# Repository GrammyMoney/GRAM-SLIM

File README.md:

# GRAM Slim

# Introduction 
**GRAM Slim** is a modular low-profile 21-button controller designed for Smash and FGC games. It has the standard pinout for firmwares like HayBox and Pico-Rectangle, and is also compatible with more fleshed-out FGC firmwares like GP2040-CE. With industrial design from GRAM, and PCB designed in collaboration with Quark.Works, this guide goes over a DIY-friendly approach to building the original GRAM Slim, and future guides/repos may hold remixes and modifications.

**If you would like to support the developer of this project, consider purchasing parts like buttons, PCBs, USB-C to GCC cables, and official GRAM builds at [GRAMCTRL.COM](https://www.gramctrl.com) rather than a fab house.**

Included Files
-
Included in this repo is all the files needed to get started with a simple GRAM Slim build:
- **GRAM Slim Frame .stl files**
- **Fab files for top and bottom panels**
- **Template DXF** for customizing top and bottom panels
- **GRAM 24mm keycap button .stl files**

Additional Information
-
If you want more info around GRAM builds, both open source and official builds, please join the [GRAM Digital Controllers Discord](https://discord.gg/6TuHw2r2X4) to ask questions and work with the community! I would love to see people creating new interesting designs, and building upon the initial framework.

Thanks & Acknowledgements
-
There are several people who made this project possible, either directly or indirectly.
- [Quark](https://twitter.com/quark_works), who did the PCB design on this and many other GRAM projects.
- [Bjart](https://twitter.com/bjartskular2), who developed the OFOF1 chassis, which was the initial development for a lot of the ideas explored in this build, including using PCB fabs for the panels, and the general idea of stacking two panels on a frame for the enclosure.
- My life and business partner [BRUISES](https://twitter.com/bruisesxo), who has turned GRAM into what it is today, and had incredible patience with me as I toiled away at my computer late into the night designing this thing.

# Ordering & Customization Guide
While most of these files are universal and can be used at any fab house, **JLCPCB** has become the de-facto standard for DIY box manufacturing. This is due to their hyper-affordable pricing and low minimum order quantity.

Bill of Materials
-
Per GRAM Slim, you will need (some files can be made using this repository, but I will link to places to purchase them if you would like to avoid MOQs)
- 1 x [GRAM Slim PCB](https://gramctrl.com/products/gram-slim-pcb)
- 1 x set of [Top/Bottom panels](https://gramctrl.com/products/gram-slim-aluminum-panels)
- 21 x [Kailh Choc V1 switches](https://www.moergo.com/products/kailh-choc-v1-key-switches-red-brown-white-pro-red-20-pack?variant=45328736780561) (Red, Red Pro, and Whites are all great choices)
- 21 x [PG1350 Hotswap Sockets](https://mkultra.click/kailh-hotswap-sockets)
- 21 x [GRAM 24mm Choc Keycap Buttons](https://gramctrl.com/products/gram-24mm-choc-v1-keycap-buttons)
- 1 x GRAM Slim Frame
- 7 x [M5x0.8 8mm Low-Profile Socket Head Screws](https://www.mcmaster.com/92855A507)
- 7 x [M5x0.8 Round-Base Weld Nuts](https://www.mcmaster.com/90563A680)

*Optional*
- USB-C to GCC cable for console/adapter play

Tools Needed
-
This guide assumes a level of knowledge on soldering and computer literacy. General tool requirements are:
- Soldering iron
- Solder
- USB-C to USB-A cable
- 3mm hex key/allen wrench
- Pliers
- Patience :)

The PCB
-
The PCB Fabrication files should come in the form of a *Gerber ZIP file* and *bom/cpl files* (usually in Excel spreadsheet formats).

Drag them into the "Upload Gerbers" box at JLCPCB and this page will pop up:

Here you can change the color of the PCB. Green is the fastest and cheapest from JLC, but their black PCBs look *siiiiiick*. The only setting I recommend you change is to check "**Yes**" on *Confirm Production file*. This allows for any mistakes to be ironed out by their engineers.

Towards the bottom of the page, you want to turn on the switch for **PCB ASSEMBLY**.

Make sure you are assembling the *Bottom Side* of the PCB, and make sure to set *Confirm Parts Placement* to "**Yes**". None of the advanced options need to be changed.

Upon confirming your PCB Assembly options, you'll be taken to the Assembly wizard. Clicking next will give you a location to upload the *BOM* and *CPL* files (*CPL* is referred to as *Positions* in the GRAM Slim files). Once you click through, you'll be brought to you BOM list.

This will allow you to modify parts if there's any low stock. There's a line at the bottom for CH1-CH21 with some red text. This is for assembling hotswap sockets, which is not recommended for JLC, as you have to preorder them. when you click **next**, continue by clicking *Do not place*.

The wizard looks intimidating, but good news! Since you're confirming part placement, the JLC engineers will fix any errors. Just go ahead and continue.

There you have it! Your PCB is ready to order. As of the time of this writing, a set of 5 assembled boards costs $56.07 before shipping.

The Panels
-
The process of ordering aluminum panels from JLC is similar to the PCB ordering process, but much simpler. Start by dragging the **GRAM Slim Top** Zip file into the JLC upload window. We want an aluminum PCB, 1.6mm. You can choose either white or black coating (white tends to be glossy, black is matte but a fingerprint magnet). 

Under High-spec Options, make sure to remove order number, or else they'll put an ugly serial number on the panel.

Once you save to cart, you'll see this screen:

Here you can add the **GRAM Slim Bottom** Zip file, and it will copy all your settings from the Top panel. Save to cart, and you're ready to check out with your PCBs!

*Note: JLCPCB cannot transact PCB and 3D printing orders together, so place this order, then move on to 3D printing.*

The Frame
-
The frame file is pretty self explanatory. Just go into JLC's 3D printing section, drop the STL file in, and choose your material. I recommend black Resin, but LEDO 6060 is a great, low cost alternative. The only material I recommend against is the textured Nylon options, as the tolerances between the frame and panels are extremely tight, and the texture could interfere with that. make sure the surface finish is set to *sanded*.

The Buttons
-
In the files, there are two versions. A single button for reference, and a 10x .STL file for mass printing at JLC. Each GRAM Slim requires 2.1 prints, so to make the minimum order quantity of 5 PCBs, you will need to order 11 prints of it.

The 10x file is the ideal for JLC, as it minimizes cost. JLC may reach out to you and add some cost (0.30/pc) for small parts. This is normal.

The buttons have been tested in 4 material materials:
- **LEDO 6060** (natural white, most cost-effective option, goes well with matching frame and black aluminum panels)
- **Black Resin** (matte grayish-black, goes well with both black and white panels)
- **PA12-HP Nylon** (Only slightly more expensive for buttons, but gives an amazing textured finish, very premium feel)
- **8001 Transparent Resin** (Really cool, really expensive)

# Build Guide

Building the GRAMv2 is relatively straightforward, but an updated in-depth build guide (including a video!) is currently in the works.

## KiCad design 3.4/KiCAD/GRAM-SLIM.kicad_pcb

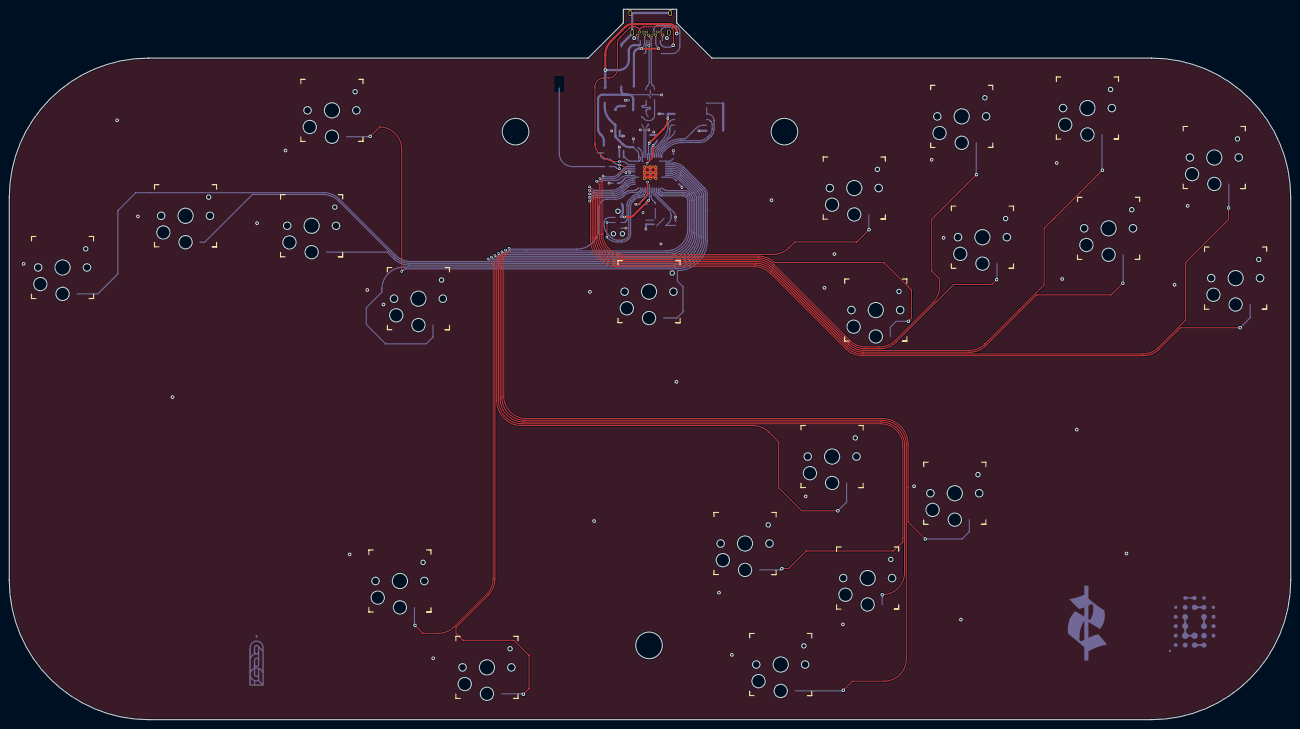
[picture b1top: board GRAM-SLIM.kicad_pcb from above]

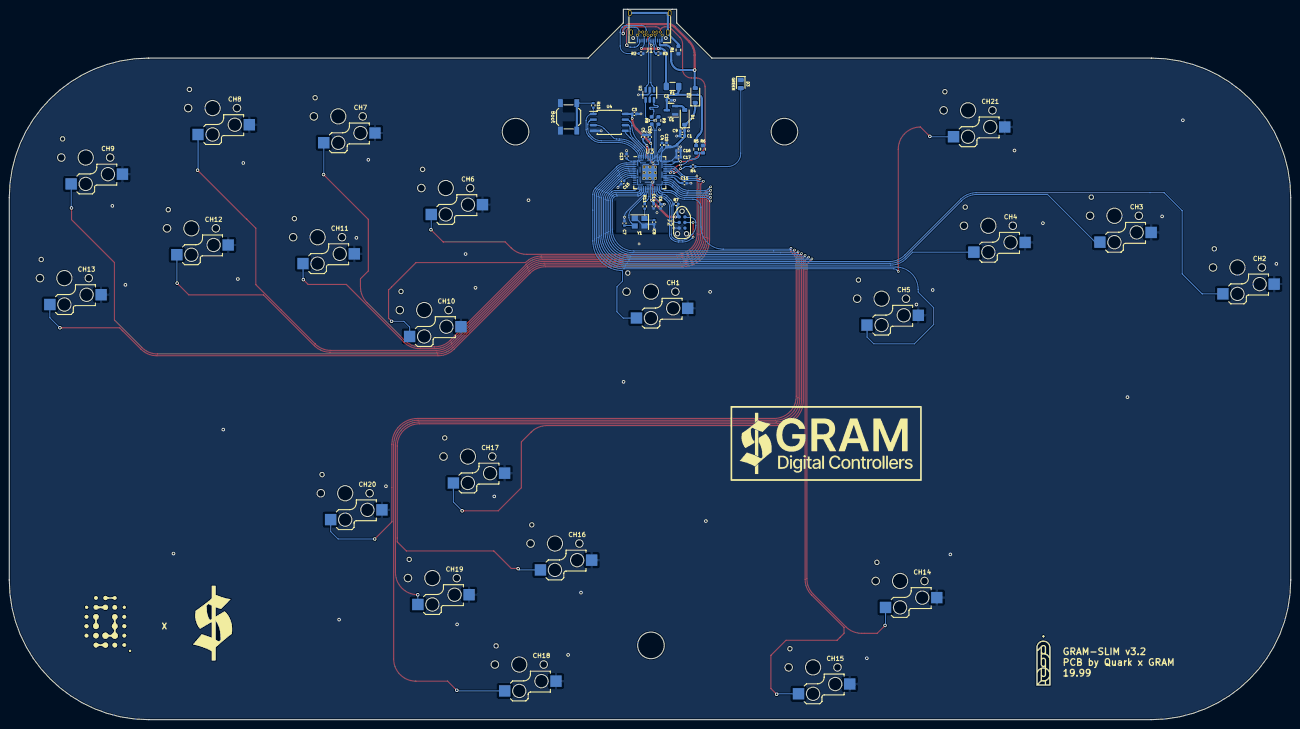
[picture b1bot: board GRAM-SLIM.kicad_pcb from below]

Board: 2 copper layers, 288.8 x 160.1 mm, 63 parts (42 on the bottom side), 54 nets.

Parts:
C1, C2, C4, C10: 1uF; C_0402_1005Metric
C3, C5, C6, C11, C12, C13, C14, C15, C16, C17: 100nF; C_0402_1005Metric
C7, C8: 22pF; C_0402_1005Metric
C9: 10uF; C_0402_1005Metric
CH1, CH2, CH3, CH4, CH5, CH6, CH7, CH8, CH9, CH10, CH11, CH12, CH13, CH14, CH15, CH16, CH17, CH18, CH19, CH20, CH21: choc_SW_HS; Kailh_socket_PG1350
D1, D2: Schottky Diode; D_SOD-123
D3: GREEN; LED_0805_2012Metric
F1: 500 mA; Fuse_1206_3216Metric
H1: qw-logo; qw new logo silk + copper md
H2: 1999 logo; 1999 logo md
J1: USB C Connector; TYPE-C_24P_QCHT
J2: JTAG_TC2030; CON_TC2030_outlined
R1: 1M; R_0603_1608Metric
R2, R3: 5.1k; R_0402_1005Metric
R4: 470; R_0402_1005Metric
R5: 5.6k; R_0603_1608Metric
R6: 10k; R_0603_1608Metric
R7: 10k; R_0402_1005Metric
R8, R9: 27; R_0603_1608Metric
R10, R11: 1k; R_0402_1005Metric
SW1: Boot; SW_SPST_SKQG_WithStem
U1: XC6206; SOT-23
U2: USBLC6-2SC6; SOT-23-6
U3: RP2040; RP2040-QFN-56
U4: W25Q128JVS; SOIC-8_5.23x5.23mm_P1.27mm
Y1: 12MHz; Crystal_SMD_3225-4Pin_3.2x2.5mm

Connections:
3vCable: D2.2 (A), J1.A2 (TX1+), J1.B2 (TX2+)
+1V1: C4.1, C5.1, C6.1, U3.23 (DVDD), U3.45 (VREG_VOUT), U3.50 (DVDD)
+3V3: C1.2, C3.1, C9.1, C10.1, C11.1, C12.1, C13.1, C14.1, C15.1, C16.1, C17.1, D1.1 (K), D2.1 (K), J2.1 (VCC), R7.1, U3.1 (IOVDD), U3.10 (IOVDD), U3.22 (IOVDD), U3.33 (IOVDD), U3.42 (IOVDD), U3.43 (ADC_AVDD), U3.44 (VREG_VIN), U3.48 (USB_VDD), U3.49 (IOVDD), U4.8 (VCC)
+5V: C2.2, F1.2, R5.1, U1.3 (VI), U2.5 (VBUS)
/D_+: R8.2, U3.47 (D+)
/D_-: R9.2, U3.46 (D-)
/XTAL_O: C8.2, R11.1, Y1.1
/~USB_BOOT: R10.1, SW1.2
A: CH19.1, U3.17 (GPIO14)
B: CH10.1, U3.38 (GPIO26/ADC0)
CS: R10.2, U3.56 (QSPI_SS_N), U4.1 (~CS)
C_DN: CH18.1, U3.18 (GPIO15)
C_LT: CH16.1, U3.16 (GPIO13)
C_RT: CH20.1, U3.27 (GPIO16)
C_UP: CH17.1, U3.15 (GPIO12)
D+: R8.1, U2.6 (I/O1)
D-: R9.1, U2.4 (I/O2)
DATA: J1.A11 (RX2+), J1.B11 (RX1+), U3.40 (GPIO28/ADC2)
DBUS+: J1.A6 (D+), J1.B6 (D+), U2.1 (I/O1)
DBUS-: J1.A7 (D-), J1.B7 (D-), U2.3 (I/O2)
DOWN: CH4.1, U3.5 (GPIO3)
EXTRA: CH21.1, U3.3 (GPIO1)
GND: C1.1, C2.1, C3.2, C4.2, C5.2, C6.2, C7.1, C8.1, C9.2, C10.2, C11.2, C12.2, C13.2, C14.2, C15.2, C16.2, C17.2, CH1.2, CH2.2, CH3.2, CH4.2, CH5.2, CH6.2, CH7.2, CH8.2, CH9.2, CH10.2, CH11.2, CH12.2, CH13.2, CH14.2, CH15.2, CH16.2, CH17.2, CH18.2, CH19.2, CH20.2, CH21.2, D3.1 (K), J1.A1 (GND), J1.A12 (GND), J1.B1 (GND), J1.B12 (GND), J2.5 (GND), R1.1, R2.1, R3.2, R6.2, SW1.1, U1.1 (GND), U2.2 (GND), U3.19 (TESTEN), U3.57 (GND), U4.4 (GND), Y1.2, Y1.4
L: CH2.1, U3.7 (GPIO5)
LEFT: CH3.1, U3.6 (GPIO4)
LS: CH8.1, U3.31 (GPIO20)
M1: CH14.1, U3.8 (GPIO6)
M2: CH15.1, U3.9 (GPIO7)
MS: CH9.1, U3.29 (GPIO18)
unnamed: D1.2 (A), U1.2 (VO)
unnamed: D3.2 (A), R4.2
unnamed: F1.1, J1.A4 (VBUS), J1.A9 (VBUS), J1.B4 (VBUS), J1.B9 (VBUS)
unnamed: J1.A5 (CC1), R3.1
unnamed: J1.B5 (CC2), R2.2
unnamed: J1.S1 (SHIELD), R1.2
PICO_LED: R4.1, U3.37 (GPIO25)
QSPI_CLK: U3.52 (QSPI_SCLK), U4.6 (CLK)
R: CH6.1, U3.39 (GPIO27/ADC1)
RIGHT: CH5.1, U3.4 (GPIO2)
SD0: U3.53 (QSPI_SD0), U4.5 (DI(IO0))
SD1: U3.55 (QSPI_SD1), U4.2 (DO(IO1))
SD2: U3.54 (QSPI_SD2), U4.3 (IO2)
SD3: U3.51 (QSPI_SD3), U4.7 (IO3)
START: CH1.1, U3.2 (GPIO0)
SWCLK: J2.4 (SWCLK), U3.24 (SWCLK)
SWD: J2.2 (SWDIO), U3.25 (SWDIO)
UP: CH13.1, U3.28 (GPIO17)
VBUS_SENSE: R5.2, R6.1, U3.36 (GPIO24)
X: CH11.1, U3.32 (GPIO21)
XTAL_IN: C7.2, U3.20 (XTAL_IN), Y1.3
XTAL_OUT: R11.2, U3.21 (XTAL_OUT)
Y: CH7.1, U3.34 (GPIO22)
Z: CH12.1, U3.30 (GPIO19)
~RESET: J2.3 (~RST), R7.2, U3.26 (~RUN)

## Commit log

2023-05-24 Everything but the panels
2023-05-25 Added PCB with integrated RP2040
2023-06-03 Added v3.1 files
2023-06-17 added v3.4
2023-08-20 Prepared for public release
    LETS GOOOOOO
2023-08-20 Added DXF templates for faceplates
2023-08-20 added gerbers for PCB
2023-08-21 Added Tsunami
2023-08-21 for readme
2023-10-22 Updated Panel Files for Clarity
2023-10-22 removed punctuation for JLC
2023-10-23 Developed ordering guide
2023-12-18 added better buttons
2023-12-18 Rename v17 basically v2 buttons x10.stl to v2 buttons printable x10.stl
2023-12-18 moved STL
2024-06-21 Create LICENSE
